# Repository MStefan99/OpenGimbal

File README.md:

# OpenGimbal

## Smooth footage made hackable

**Open source gimbal you can build, tweak and extend to match all your filming needs**

Note: OpenGimbal is undergoing final preparations before the first public release. Documentation is still being written
and hardware designs are undergoing final testing and will be published shortly.

## Highlights
### Hackable
Add as many motors as you like, control them over USB or UART and mount it anywhere you like. Use it as is or integrate it into your own project.

### Ready to use
Between firmware and software, PCB designs and 3D-printable parts, everything is ready for you to go.
Built-in calibrations and checks get the headache out of the setup process.

### Small but mighty
Film for 10 hours on a single charge, enjoy 15 watts of peak power and standby time measured in years.

## Introduction

A gimbal is a device that lets you shoot smooth video by canceling out unwanted camera movements. They come in many shapes and sizes, from tiny ones with integrated cameras to heavy-duty
devices for DSLRs or film cameras, often mounted on drones or cranes.

OpenGimbal can be all of those! The philosophy behind OpenGimbal is to make every single part customizable and extensible for your own needs.
The provided designs allow you to get started with a small but powerful smartphone gimbal in a few hours, but you can always adapt them to your own needs.

OpenGimbal is not just handy for gimbals, though. Grab included designs and firmware for brushless motor controllers and make anything you want move!

## Features

- Includes everything you need to get started: PCB designs, 3D models, firmware, software and documentation.
- Film for 10 hours on a single 18650 battery or add more capacity!
- Enjoy 15 watts of peak power with the provided controller or bring your own for up to 22 watts per motor!
- Stop worrying about the battery with USB-C charging and standby time measured in years.
- Every part can be customized, left out or replaced with your own designs to fit your needs.
- Can be easily controlled by your own software or hardware over USB or UART.
- Stock or custom, just point and shoot instantly without worrying about math with the fast IK solver.
- Easily customizable firmware with ready-made drivers, simple API and extensive documentation.
- Completely open source!

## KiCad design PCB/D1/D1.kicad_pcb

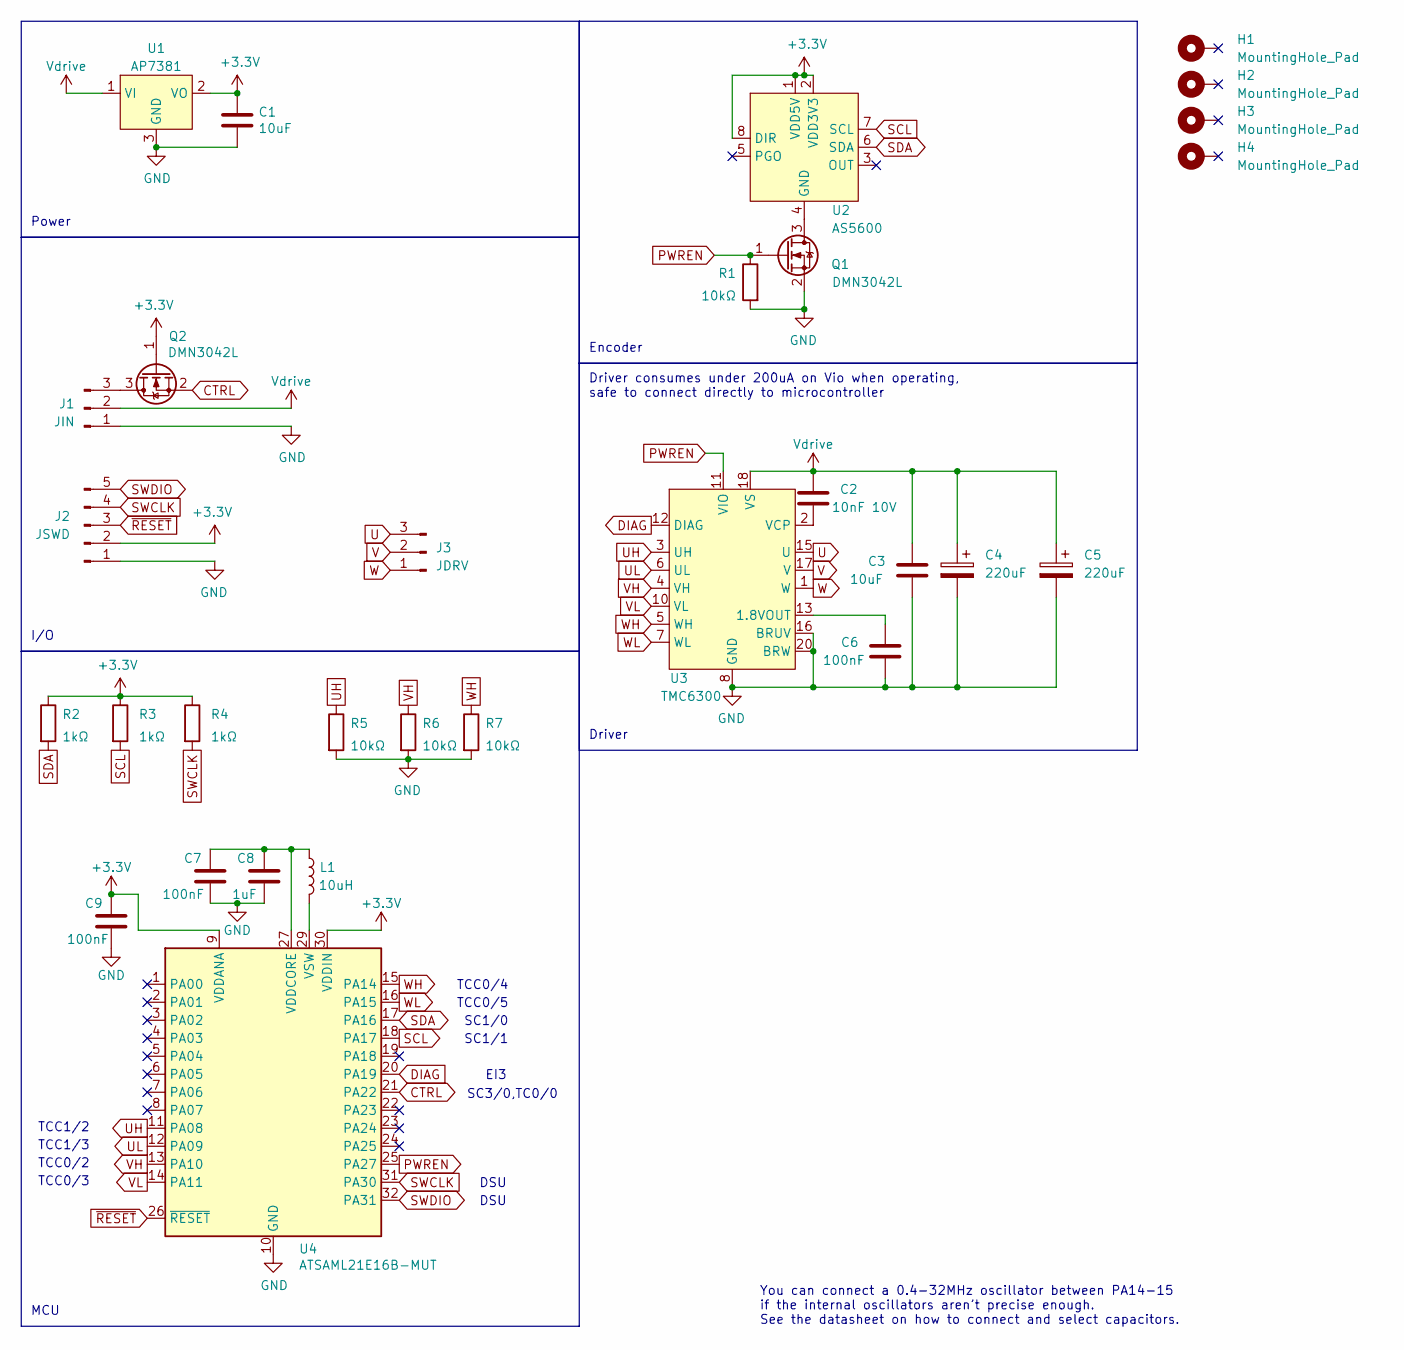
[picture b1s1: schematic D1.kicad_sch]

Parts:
C1, C3: 10uF; C_0603_1608Metric
C2: 10nF 10V; C_0603_1608Metric
C4, C5: 220uF; CP_EIA-7343-43_Kemet-X
C6, C7, C9: 100nF; C_0603_1608Metric
C8: 1uF; C_0603_1608Metric
H1, H2, H3, H4: MountingHole_Pad; MountingHole_3.2mm_M3_Pad
J1: JIN; PinHeader_1x03_P2.54mm_Vertical
J2: JSWD; PinHeader_1x05_P2.54mm_Vertical
J3: JDRV; PinHeader_1x03_P2.54mm_Vertical
L1: 10uH; C_0603_1608Metric
Q1, Q2: DMN3042L; SOT-23
R1, R5, R6, R7: 10kΩ; R_0603_1608Metric
R2, R3, R4: 1kΩ; R_0603_1608Metric
U1: AP7381; SOT-23
U2: AS5600; SOIC-8_3.9x4.9mm_P1.27mm
U3: TMC6300; QFN-20-1EP_3x3mm_P0.4mm_EP1.65x1.65mm
U4: ATSAML21E16B-MUT; QFN-32-1EP_5x5mm_P0.5mm_EP3.45x3.45mm

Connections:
+3.3V: C1.1, C9.1, J2.2, Q2.1 (G), R2.1, R3.1, R4.1, U1.2 (VO), U2.1 (VDD5V), U2.2 (VDD3V3), U2.8 (DIR), U4.9 (VDDANA), U4.30 (VDDIN)
CTRL: Q2.2 (S), U4.21 (PA22)
DIAG: U3.12 (DIAG), U4.20 (PA19)
GND: C1.2, C3.2, C4.2, C5.2, C6.2, C7.2, C8.2, C9.2, J1.1, J2.1, Q1.2 (S), R1.2, R5.2, R6.2, R7.2, U1.3 (GND), U3.8 (GND), U3.9 (GND), U3.14 (GND), U3.16 (BRUV), U3.20 (BRW), U3.21 (PAD), U4.10 (GND), U4.28 (GND), U4.33 (GND)
unnamed: J1.3, Q2.3 (D)
unnamed: Q1.3 (D), U2.4 (GND)
unnamed: C6.1, U3.13 (1.8VOUT)
unnamed: C2.2, U3.2 (VCP)
unnamed: C7.1, C8.1, L1.1, U4.27 (VDDCORE)
unnamed: L1.2, U4.29 (VSW)
PWREN: Q1.1 (G), R1.1, U3.11 (VIO), U4.25 (PA27)
SCL: R3.2, U2.7 (SCL), U4.18 (PA17)
SDA: R2.2, U2.6 (SDA), U4.17 (PA16)
SWCLK: J2.4, R4.2, U4.31 (PA30)
SWDIO: J2.5, U4.32 (PA31)
U: J3.3, U3.15 (U)
UH: R5.1, U3.3 (UH), U4.11 (PA08)
UL: U3.6 (UL), U4.12 (PA09)
V: J3.2, U3.17 (V)
VH: R6.1, U3.4 (VH), U4.13 (PA10)
VL: U3.10 (VL), U4.14 (PA11)
Vdrive: C2.1, C3.1, C4.1, C5.1, J1.2, U1.1 (VI), U3.18 (VS)
W: J3.1, U3.1 (W)
WH: R7.1, U3.5 (WH), U4.15 (PA14)
WL: U3.7 (WL), U4.16 (PA15)
~RESET: J2.3, U4.26 (~RESET)

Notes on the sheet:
Driver
SC1/0
TCC1/2
You can connect a 0.4-32MHz oscillator between PA14-15 if the internal oscillators aren't precise enough. See the datasheet on how to connect and select capacitors.
I/O
TCC0/3
Encoder
TCC1/3
DSU
TCC0/5
Power
Driver consumes under 200uA on Vio when operating, safe to connect directly to microcontroller
TCC0/4
SC1/1
SC3/0,TC0/0
MCU
TCC0/2
EI3

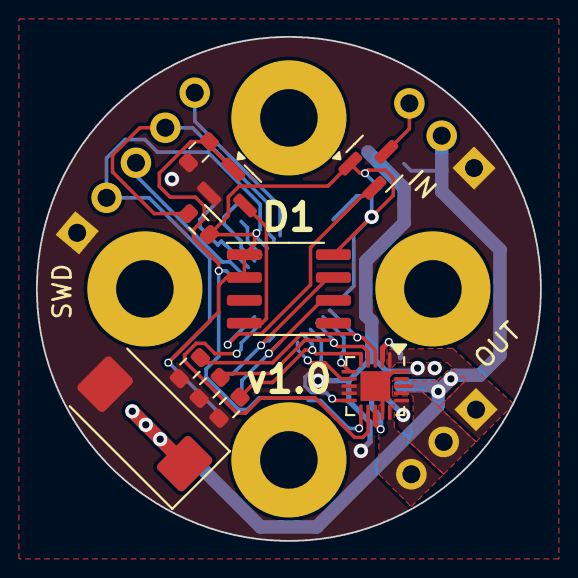
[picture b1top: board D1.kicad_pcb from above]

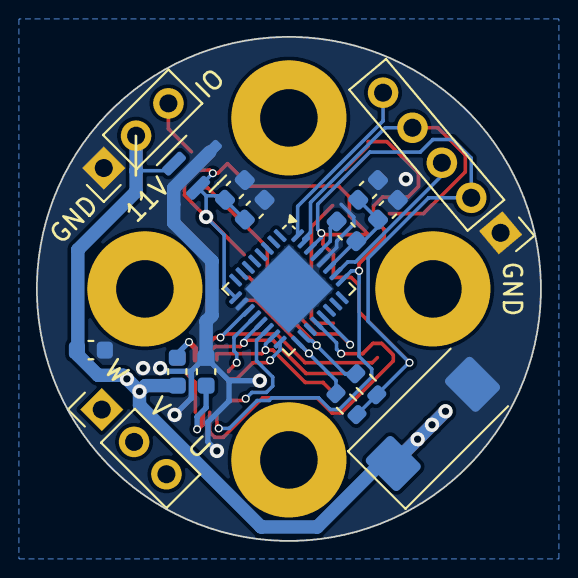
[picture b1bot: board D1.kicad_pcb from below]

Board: 2 copper layers, 28.0 x 28.0 mm, 30 parts (16 on the bottom side), 26 nets.

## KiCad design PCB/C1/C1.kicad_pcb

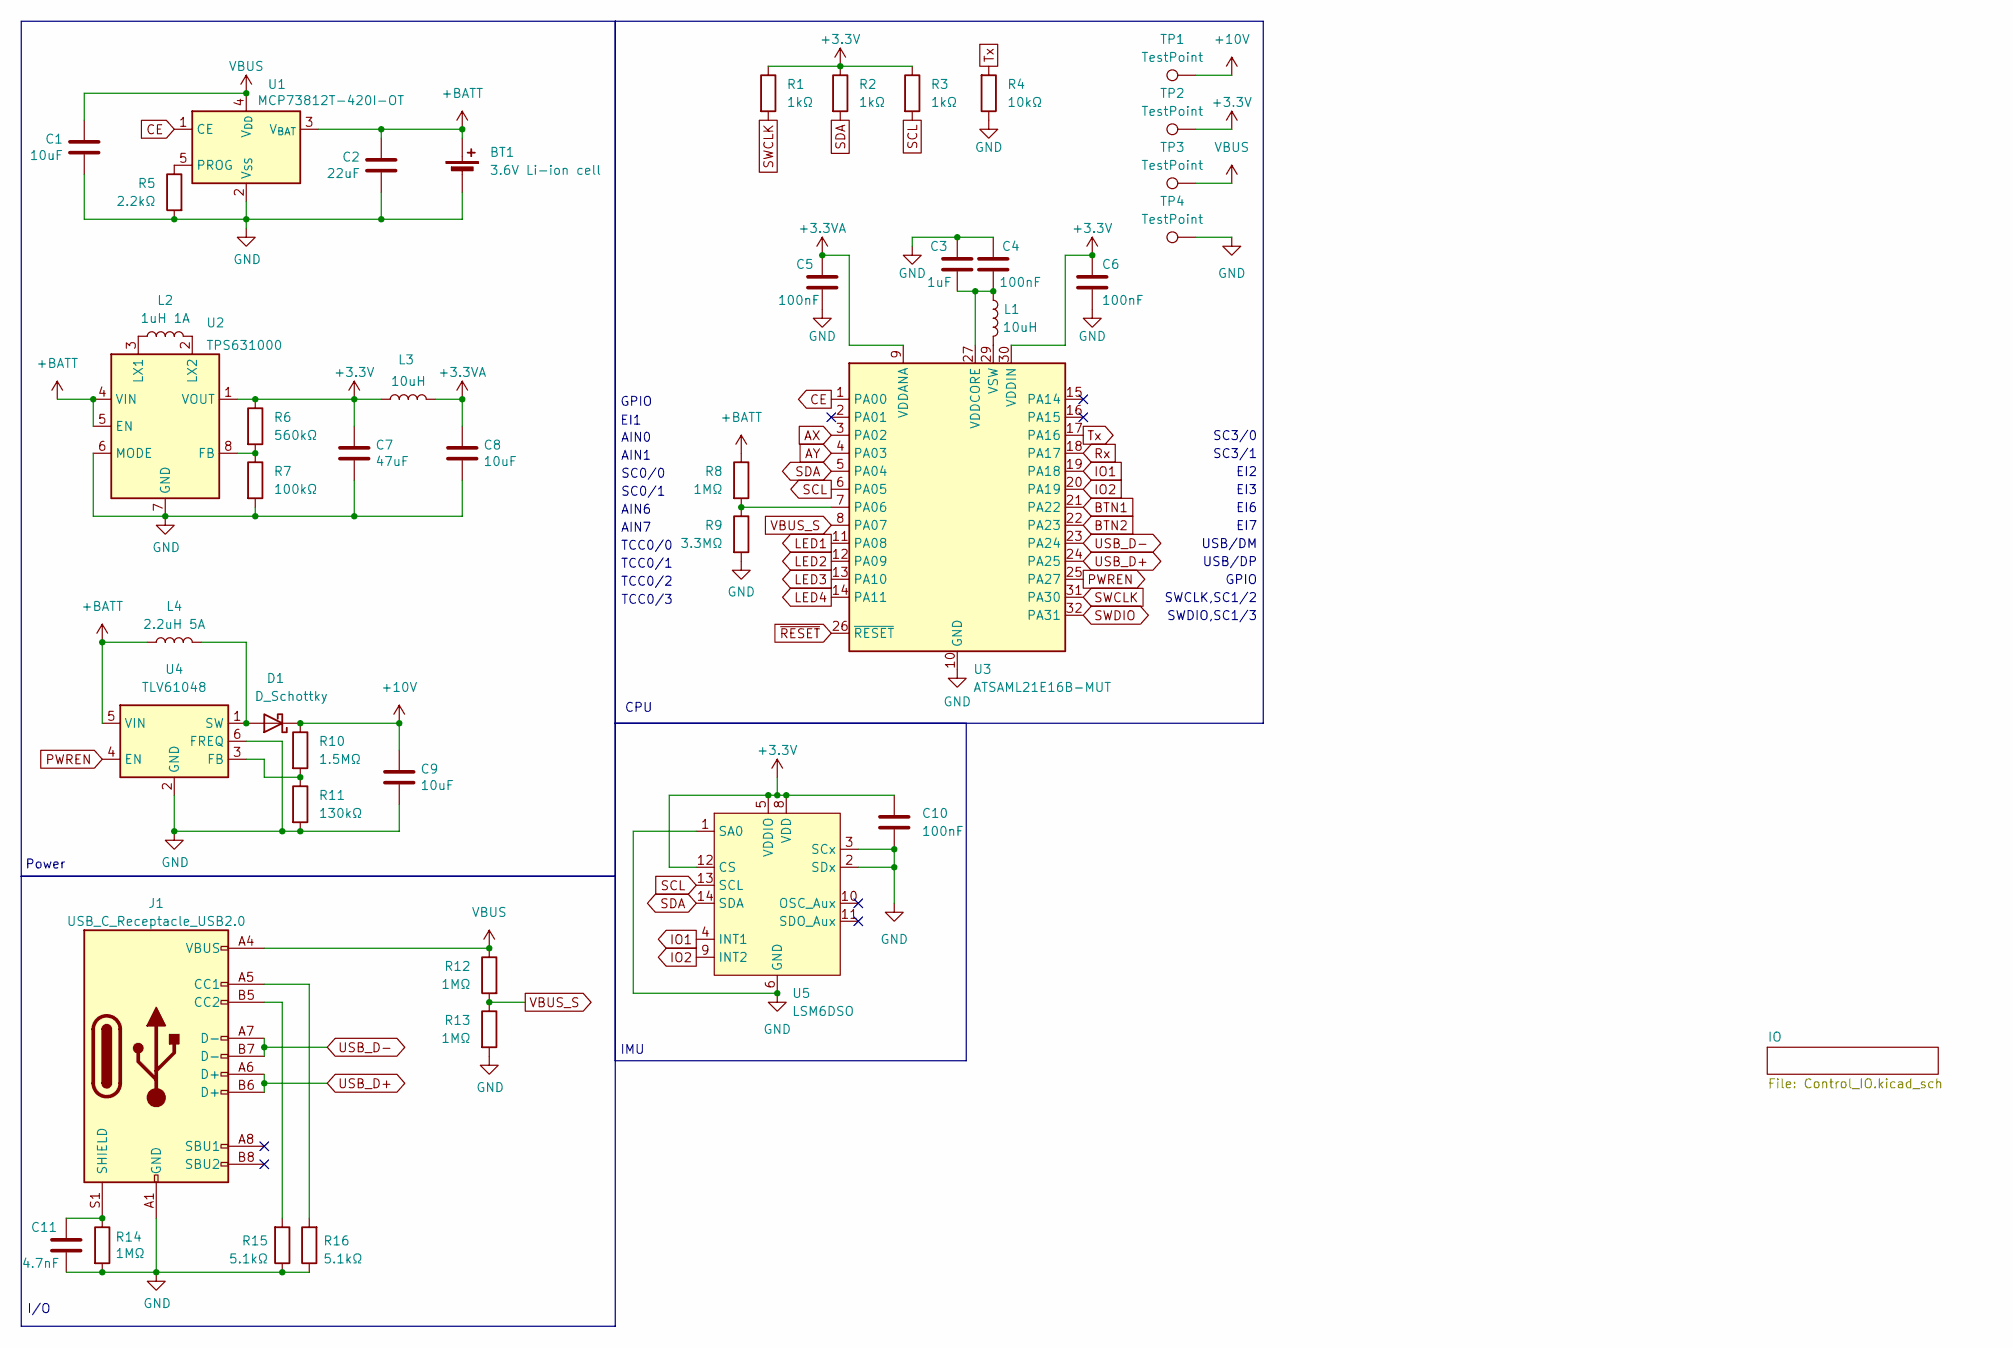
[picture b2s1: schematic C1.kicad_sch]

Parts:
BT1: 3.6V Li-ion cell; PinHeader_1x02_P2.54mm_Vertical
C1, C8, C9: 10uF; C_0603_1608Metric
C2: 22uF; C_0603_1608Metric
C3: 1uF; C_0603_1608Metric
C4, C5, C6, C10: 100nF; C_0603_1608Metric
C7: 47uF; C_0603_1608Metric
C11: 4.7nF; C_0603_1608Metric
D1: D_Schottky; D_SMA
J1: USB_C_Receptacle_USB2.0; USB4080
L1, L3: 10uH; C_0603_1608Metric
L2: 1uH 1A; L_0805_2012Metric
L4: 2.2uH 5A; L_TDK_VLS6045EX_VLS6045AF
R1, R2, R3: 1kΩ; R_0603_1608Metric
R4: 10kΩ; R_0603_1608Metric
R5: 2.2kΩ; R_0603_1608Metric
R6: 560kΩ; R_0603_1608Metric
R7: 100kΩ; R_0603_1608Metric
R8, R12, R13, R14: 1MΩ; R_0603_1608Metric
R9: 3.3MΩ; R_0603_1608Metric
R10: 1.5MΩ; R_0603_1608Metric
R11: 130kΩ; R_0603_1608Metric
R15, R16: 5.1kΩ; R_0603_1608Metric
TP1, TP2, TP3, TP4: TestPoint; TestPoint_Pad_D2.5mm
U1: MCP73812T-420I-OT; SOT-23-5
U2: TPS631000; SOT-583-8
U3: ATSAML21E16B-MUT; QFN-32-1EP_5x5mm_P0.5mm_EP3.45x3.45mm
U4: TLV61048; SOT-23-6
U5: LSM6DSO

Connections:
+3.3V: C6.1, C7.1, C10.2, L3.1, R1.1, R2.1, R3.1, R6.1, TP2.1, U2.1 (VOUT), U3.30 (VDDIN), U5.5 (VDDIO), U5.8 (VDD), U5.12 (CS); also elsewhere on the board
+3.3VA: C5.1, C8.1, L3.2, U3.9 (VDDANA)
+10V: C9.1, D1.1 (K), R10.1, TP1.1; also elsewhere on the board
+BATT: BT1.1 (+), C2.1, L4.1, R8.1, U1.3 (V_{BAT}), U2.4 (VIN), U2.5 (EN), U4.5 (VIN)
AX: U3.3 (PA02); also elsewhere on the board
AY: U3.4 (PA03); also elsewhere on the board
BTN1: U3.21 (PA22); also elsewhere on the board
BTN2: U3.22 (PA23); also elsewhere on the board
CE: U1.1 (CE), U3.1 (PA00)
GND: BT1.2 (-), C1.2, C2.2, C3.1, C4.1, C5.2, C6.2, C7.2, C8.2, C9.2, C10.1, C11.2, J1.A1 (GND), J1.A12 (GND), J1.B1 (GND), J1.B12 (GND), R4.1, R5.2, R7.2, R9.2, R11.2, R13.2, R14.2, R15.1, R16.1, TP4.1, U1.2 (V_{SS}), U2.6 (MODE), U2.7 (GND), U3.10 (GND), U3.28 (GND), U3.33 (GND), U4.2 (GND), U4.6 (FREQ), U5.1 (SA0), U5.2 (SDx), U5.3 (SCx), U5.6 (GND), U5.7 (GND); also elsewhere on the board
IO1: U3.19 (PA18), U5.4 (INT1)
IO2: U3.20 (PA19), U5.9 (INT2)
LED1: U3.11 (PA08); also elsewhere on the board
LED2: U3.12 (PA09); also elsewhere on the board
LED3: U3.13 (PA10); also elsewhere on the board
LED4: U3.14 (PA11); also elsewhere on the board
unnamed: D1.2 (A), L4.2, U4.1 (SW)
unnamed: J1.A5 (CC1), R16.2
unnamed: J1.B5 (CC2), R15.2
unnamed: C11.1, J1.S1 (SHIELD), R14.1
unnamed: R5.1, U1.5 (PROG)
unnamed: R6.2, R7.1, U2.8 (FB)
unnamed: L2.1, U2.3 (LX1)
unnamed: L2.2, U2.2 (LX2)
unnamed: R8.2, R9.1, U3.7 (PA06)
unnamed: C3.2, C4.2, L1.1, U3.27 (VDDCORE)
unnamed: L1.2, U3.29 (VSW)
unnamed: R10.2, R11.1, U4.3 (FB)
PWREN: U3.25 (PA27), U4.4 (EN); also elsewhere on the board
Rx: U3.18 (PA17); also elsewhere on the board
SCL: R3.2, U3.6 (PA05), U5.13 (SCL)
SDA: R2.2, U3.5 (PA04), U5.14 (SDA)
SWCLK: R1.2, U3.31 (PA30); also elsewhere on the board
SWDIO: U3.32 (PA31); also elsewhere on the board
Tx: R4.2, U3.17 (PA16); also elsewhere on the board
USB_D+: J1.A6 (D+), J1.B6 (D+), U3.24 (PA25)
USB_D-: J1.A7 (D-), J1.B7 (D-), U3.23 (PA24)
VBUS: C1.1, J1.A4 (VBUS), J1.A9 (VBUS), J1.B4 (VBUS), J1.B9 (VBUS), R12.1, TP3.1, U1.4 (V_{DD})
VBUS_S: R12.2, R13.1, U3.8 (PA07)
~RESET: U3.26 (~RESET); also elsewhere on the board

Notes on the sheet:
EI2
EI6
USB/DM
TCC0/1
SC0/1
AIN7
AIN6
SWDIO,SC1/3
EI3
AIN1
TCC0/3
GPIO
EI7
TCC0/0
IMU
USB/DP
EI1
TCC0/2
Power
AIN0
SC3/0
SC3/1
SWCLK,SC1/2
SC0/0
I/O
CPU

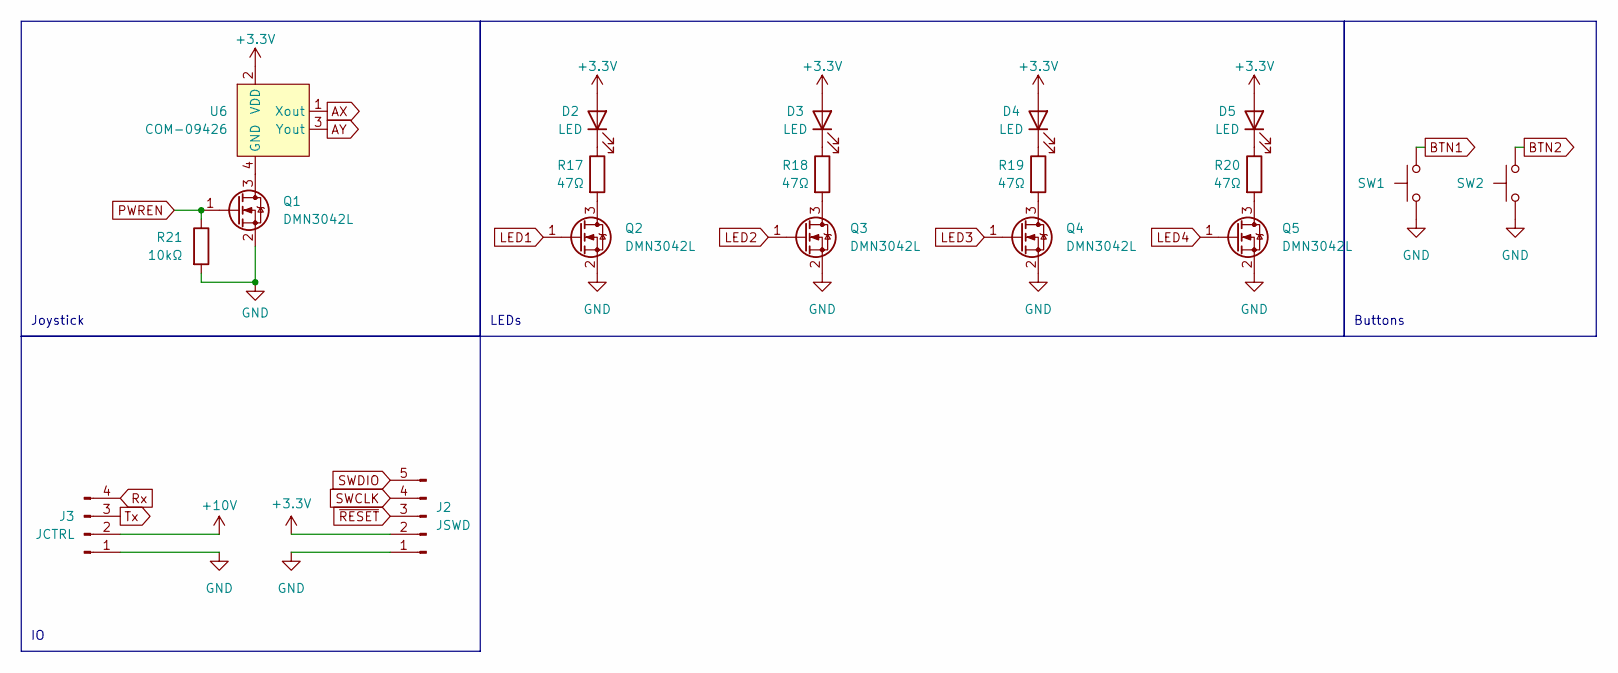
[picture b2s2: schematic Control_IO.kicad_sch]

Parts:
D2, D3, D4, D5: LED; D_0603_1608Metric
J2: JSWD; PinHeader_1x05_P2.54mm_Vertical
J3: JCTRL; PinHeader_1x04_P2.54mm_Vertical
Q1, Q2, Q3, Q4, Q5: DMN3042L; SOT-23
R17, R18, R19, R20: 47Ω; R_0603_1608Metric
R21: 10kΩ; R_0603_1608Metric
SW1, SW2: SW_Push; Switch
U6: COM-09426; COM-09426_NoHoles

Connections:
+3.3V: D2.2 (A), D3.2 (A), D4.2 (A), D5.2 (A), J2.2, U6.2 (VDD); also elsewhere on the board
+10V: J3.2; also elsewhere on the board
AX: U6.1 (Xout); also elsewhere on the board
AY: U6.3 (Yout); also elsewhere on the board
BTN1: SW1.2; also elsewhere on the board
BTN2: SW2.2; also elsewhere on the board
GND: J2.1, J3.1, Q1.2 (S), Q2.2 (S), Q3.2 (S), Q4.2 (S), Q5.2 (S), R21.2, SW1.1, SW2.1; also elsewhere on the board
LED1: Q2.1 (G); also elsewhere on the board
LED2: Q3.1 (G); also elsewhere on the board
LED3: Q4.1 (G); also elsewhere on the board
LED4: Q5.1 (G); also elsewhere on the board
unnamed: D2.1 (K), R17.1
unnamed: D3.1 (K), R18.1
unnamed: D4.1 (K), R19.1
unnamed: D5.1 (K), R20.1
unnamed: Q1.3 (D), U6.4 (GND)
unnamed: Q2.3 (D), R17.2
unnamed: Q3.3 (D), R18.2
unnamed: Q4.3 (D), R19.2
unnamed: Q5.3 (D), R20.2
PWREN: Q1.1 (G), R21.1; also elsewhere on the board
Rx: J3.4; also elsewhere on the board
SWCLK: J2.4; also elsewhere on the board
SWDIO: J2.5; also elsewhere on the board
Tx: J3.3; also elsewhere on the board
~RESET: J2.3; also elsewhere on the board

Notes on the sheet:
LEDs
Buttons
Joystick

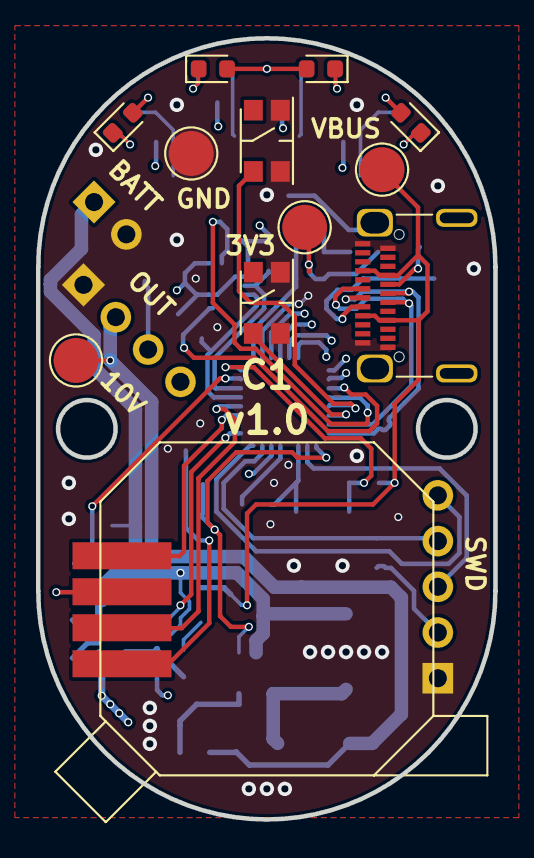
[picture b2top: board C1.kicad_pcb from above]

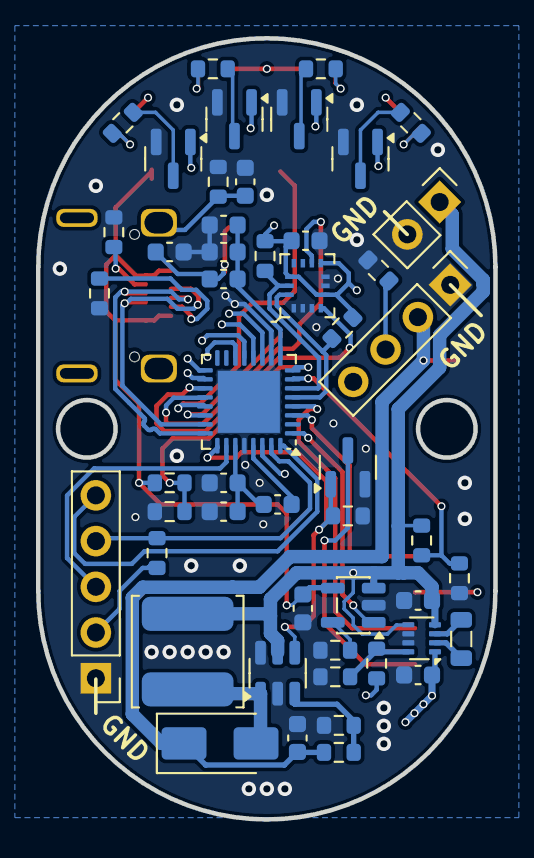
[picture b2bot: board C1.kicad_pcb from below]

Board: 4 copper layers, 25.4 x 43.4 mm, 62 parts (50 on the bottom side), 49 nets.

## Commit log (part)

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2023-07-21 wip: clock setup
2023-07-22 raised CPU and I2C frequency
2023-07-22 removed extra files
2023-07-22 implemented motor power
2023-07-23 fixed tone generation
2023-07-23 wip: dma endianness
2023-07-23 wip: applying torque
2023-07-24 added torque calculation
2023-07-24 implemented saving calibration
2023-07-24 implemented fast calibration
2023-07-27 implemented keeping position
2023-07-28 fixed amount of applied power
2023-07-28 improved NVM writes
2023-07-28 wip: sine look-up table
2023-07-29 optimized PWM generation
    switched PWM calculations to integers
2023-07-29 optimized utility functions
2023-07-29 improved saving settings
2023-07-29 implemented polarity correction
2023-07-29 improved idle PWM
2023-07-31 added PWM capture
2023-07-31 wip: PID control
2023-08-03 wip: TC capture on pin
2023-08-05 tuned motor response
2023-09-13 added demo mode
2023-09-18 added slow speed demo
2023-10-10 main firmware setup
2023-10-10 DMA setup
2023-10-10 added UART input
2023-10-10 added simple position example
2023-10-10 updated dependencies
2023-11-07 UART protocol setup
    DMA setup
    removed template library
    added ring buffer
    removed dynamic memory allocation for communication/DMA
2023-11-08 UART data structure setup
2023-11-08 added position command
2023-12-12 added control board project
2023-12-14 added turning on/off animation
    set up task scheduler
2023-12-14 fixed systick initialization
2023-12-14 updated main project
2023-12-18 wip: optimizing memory usage
2023-12-21 added battery measurement
2024-01-20 cleaned up projects
2024-01-20 wip: DMA-less UART
2024-01-21 wip: uart transfers
2024-01-22 implemented interrupt-based UART
2024-01-22 added LED PWM
2024-01-22 added brightness correction
2024-01-23 added UART transfer queue
2024-01-29 added button interrupts
2024-01-29 added uart print
2024-01-30 improved uart types
2024-01-30 set up command types
2024-01-30 added variables
2024-01-31 added multi-UART support
2024-01-31 configured communication
2024-01-31 integrated main and motor boards
2024-02-01 uart retarget setup
2024-02-05 fixed motor project config
2024-02-11 fixed uart race condition
    added task scheduler
2024-02-11 wip: time-optimal control
2024-02-12 updated project configurations
2024-02-13 fixed torque direction
    added acceleration hysteresis
2024-02-18 implemented sliding mode control
2024-02-18 cleaned up code
2024-02-18 added movement controller
2024-02-18 improved commmand parsing
2024-02-19 saving offset to NVM
2024-02-19 added more commands
2024-02-19 sleep test
2024-02-19 implemented sleep mode
2024-02-22 fixed tone period calculation
    added Node serial script
2024-02-22 added string conversion
2024-02-23 added serial port mock
2024-02-23 added calibration command
2024-02-23 fixed opening port
2024-02-23 added a motor class
2024-02-24 implemented return variable command
2024-02-24 wip: variable setup
2024-02-24 wip: response setup
2024-02-24 implemented reading and writing variables
2024-02-24 added debug flag
2024-02-24 added prettier
2024-02-24 added motor enumeration
2024-02-27 improved demo program
2024-02-29 added torque smoothing
2024-03-01 wip: gimbal equations
2024-03-01 removed time-optimal control
    Turns out that sliding mode control with torque smoothing (aka. basic low-pass filter) is so unreasonably effective it can not only replace time-optimal control but actually control the motor better.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
2024-03-03 added target velocity compensation
2024-03-03 added data visualizer projects
2024-03-04 moved enums
2024-03-04 implemented toggling power
2024-03-04 added sleep mode
2024-03-05 added low pass filter and adjustable dead zone
2024-03-13 wip: full state feedback
2024-03-14 wip: lqg
2024-03-15 wip: target filtering
2024-03-15 added interpolation demo
    added precise Node delay
    fixed position modulo
    motor code cleanup
2024-03-16 fixed target wraparound filtering
2024-04-01 added data visualizer output
2024-04-01 added numeric IK solver
2024-04-09 implemented disabling motor
2024-04-09 added haptic mode
2024-04-15 added server state handler
2024-04-16 project setup
    implemented update handlers
2024-04-17 added motor state
2024-04-17 wip: load detection
2024-04-18 implemented dual-mode controller
2024-04-18 adjusted filter frequency
    reduced number of wait states
2024-04-23 added Mahony filter
2024-04-23 mode switch improvements
2024-04-23 fixed Mahony filter
2024-04-23 added default options
    implemented multi-row writes
    temporarily removed target filter
2024-04-24 moved internal NVM variables
2024-04-24 renamed member variables
2024-04-24 wip: target interpolation
2024-04-24 fixed target wraparound
2024-04-24 fixed extrapolation
2024-04-25 added quaternion operations
2024-04-25 fixed quaternion difference calculation
    added initial interpolator value
    slowed down calibration
2024-04-25 added register definition generator
2024-04-25 added more registers
2024-04-26 added remaining registers
2024-04-26 added uniqueness checks
2024-04-26 added cli arguments
2024-04-26 added name check
2024-04-26 added include guards
2024-04-30 added AS5600 registers
2024-04-30 renamed namespaces
    # Conflicts:
    # gimbal-main/src/lib/inc/LSM6DSO32_regs.h
2024-04-30 replaced hardcoded values with definitions
2024-05-02 fixed IK equation
2024-05-03 copied new NVM driver
2024-05-06 fixed quaternion from euler
2024-05-11 added response type
2024-05-14 simplified options
    fixed main board nvm data
2024-05-24 added LSM303 definitions
2024-05-28 fixed pole calibration
2024-05-30 improved load handling
2024-05-30 adjusted coefficients
2024-05-30 fixed pole calibration again
2024-05-30 wip: added companion project
2024-05-30 added motor position controls
2024-05-31 added yaw smoothing
    added more motor controls
2024-06-02 added range and offset controls
2024-06-03 added remaining motor options
    improved exiting from sleep
2024-06-03 fixed difference calculation
2024-06-03 added calibration controls
2024-06-04 added readme
    moved options file
2024-06-04 fixed exiting sleep mode
2024-06-04 added pages workflow
2024-06-07 fixed yaw target wraparound
2024-06-07 removed UART framing check
2024-06-07 wip: reading joystick
2024-06-09 updated UART protocol
    changed command length
    added timeouts
2024-06-09 improved calibration
    added calibration check step and timeouts
2024-06-10 updated nvm
2024-06-10 optimized memory usage
2024-06-11 implemented mcu commands
2024-06-13 added command monitor
2024-06-14 wip: uart protocol
2024-06-17 rewrote control state machine
    fixed battery voltage range
2024-06-17 added voltage animation
2024-06-19 wip: clock and sleep setup
2024-06-20 added clang-format options
2024-06-21 changed project structure
2024-06-21 cleaned up includes
2024-06-21 set up clang-format
2024-06-21 updated NPM dependencies
2024-06-21 regenerated MHC sources
2024-06-25 added position variable
2024-06-26 implemented gimbal modes
    added startup state
2024-06-26 implemented gimbal mode change
2024-06-27 wip: camera orientations
2024-06-27 joystick setup
2024-06-28 joystick calibration setup
2024-07-01 reduced power consumption
    optimized control board power consumption
2024-07-02 improved control button logic
2024-07-02 added new camera mode
    fixed yaw offset sign
2024-08-05 fixed division by 0
2024-08-05 added axis blending
2024-08-10 added extended ranges switch
2024-08-10 added shutdown sound
2024-08-12 fixed timestamp wraparound
2024-11-22 fixed DV output
2024-11-26 added calibration failure feedback and unwind
2025-02-04 removed control UART
2025-02-04 added USB
    updated I2C driver
2025-02-05 wip: combining firmware
2025-02-06 implemented buttons and adc
2025-02-06 removed extra project
2025-02-07 fixed uart error handling
    fixed battery voltage measurement
2025-02-07 fixed offset adjustment
2025-02-07 added control board angle correction
    fixed shutdown LED effect
2025-02-13 wip: uart full-duplex mode
2025-02-18 fixed USB enumeration in sleep mode
2025-02-19 added the base for USB driver
2025-02-19 added USB encapsulation
2025-02-19 implemented motor command passthrough
2025-02-20 implemented USB passthrough
2025-02-20 fixed feature checks
2025-03-07 updated for new pinout
2025-03-07 simplified phase calculations
2025-03-07 updated I2C pinout
2025-03-10 motor ultra low power
2025-03-10 implemented variable baud rate
2025-03-10 variable baud rate in app
2025-03-10 driver low power fix
2025-03-10 improved logging
2025-03-11 wip: control board low power
2025-03-21 wip: variable baud rate
2025-03-24 fixed IMU init
2025-03-24 fixed joystick
2025-03-24 enabled ADC averaging
2025-03-24 USB fixes
2025-03-24 added uart delay
2025-03-24 implemented variable baud passthrough
2025-03-24 wip: new variables
2025-03-25 fixed disconnection handling
2025-03-25 fixed USB wakeup
2025-03-25 added speed control
2025-04-06 wip: low power
    implemented wake by interrupt
2025-04-10 wip: soft startup
2025-04-10 wip: startup skip
2025-04-11 added protocol analyzer
2025-04-11 added command classes
2025-04-11 added variable names
2025-04-11 fixed address parsing
2025-04-11 fixed command IDs
2025-04-11 fixed timeout
2025-04-11 added wake command
2025-04-11 added key error handling
2025-04-11 wip: soft start fixes
2025-04-20 fixed sercom standby entry
2025-04-22 added motor uart delay
2025-04-22 fixed motor request retries
2025-04-22 reduced power consumption
2025-04-22 improved startup smoothness
2025-04-23 improved adjusting offset
2025-04-23 fixed controls
2025-04-23 fixed joystick callback
2025-04-23 added startup effect
2025-04-23 added emergency resets
2025-04-23 added user reset
2025-04-24 removed unused scheduler
2025-04-24 added new views
2025-04-25 improved error handling
2025-04-25 refactored USB commands
2025-04-25 implemented two USB commands
2025-04-26 combined variables
2025-04-26 implemented joystick widget
2025-04-27 implemented gimbal variable commands
2025-04-27 implemented initial position
2025-04-27 enabled control view
2025-04-27 improved joystick positioning
2025-04-27 removed max speed variable
2025-04-27 improved timing control
2025-04-30 implemented USB responses
2025-04-30 reduced sensor latency
2025-04-30 added serial number
2025-04-30 fixed device info display
2025-05-01 implemented device view
2025-05-10 fixed NVM addresses
2025-05-10 added product id
2025-05-10 added voltage check before enabling
2025-05-11 refactored USB driver
2025-05-15 implemented USB suspend
2025-05-15 added option to invert motor direction
2025-05-23 added sleep timeout
2025-07-11 added sleep timeouts
2025-08-18 fixed polling interval
2025-08-21 updated IK for correct angles
2025-08-24 added IK script
2025-08-24 upadted dependencies
2025-11-17 set up docs
    updated dependencies
2025-11-17 added features
2025-11-17 minor style updates
2025-11-18 docs setup
2025-11-18 pages docs setup
2025-11-18 fixed gaps
2025-11-19 moved firmware into subfolder
2025-11-19 regenerated sources
2025-11-19 added router hook
2025-11-20 added pre-release note
2025-11-21 moved register generator
2025-11-27 updated feature highlights
2025-11-28 re-added numeric IK solver
2025-11-30 added high voltage and inverted options
2025-12-01 rewrote styles
2025-12-02 implemented host uart
2025-12-02 implemented discovery
2025-12-03 clamped angles
2025-12-03 added device info
2025-12-03 renamed classes
2025-12-03 added serial encapsulation
2025-12-03 fixed unaligned access
2025-12-03 renamed commands
2025-12-03 fixed uart length
2025-12-03 implemented companion serial support
2025-12-03 fixed response parsing
2025-12-03 removed unused imports
2025-12-03 skipped extra string requests
2025-12-03 added PCB designs
2025-12-04 minor style fixes
2025-12-04 moved tools
2025-12-04 fixed numeric IK equation
